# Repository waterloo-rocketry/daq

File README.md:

# Waterloo Rocketry Data Acquisition System

Work in progress repo for the next iteration of the WR DAQ. This revision focuses on modularity and extensibility, with the ability to easily add more sensors as required. Schematics of the last revision are in `old/`. The new system supports the following:
* Strain gauges
* 12V pressure transducers
* thermistors/RTDs based on need
* SD card logging using an Arduino
* Logging to an NI DAQ instrumentation module

The system is broken up into boards based on sensor type, with each board managing its own power requirements without the need for a central power board. Sensors can be added by populating more boards (and designing new ones to be added on if necessary). `docs/` will be populated as the project progresses.

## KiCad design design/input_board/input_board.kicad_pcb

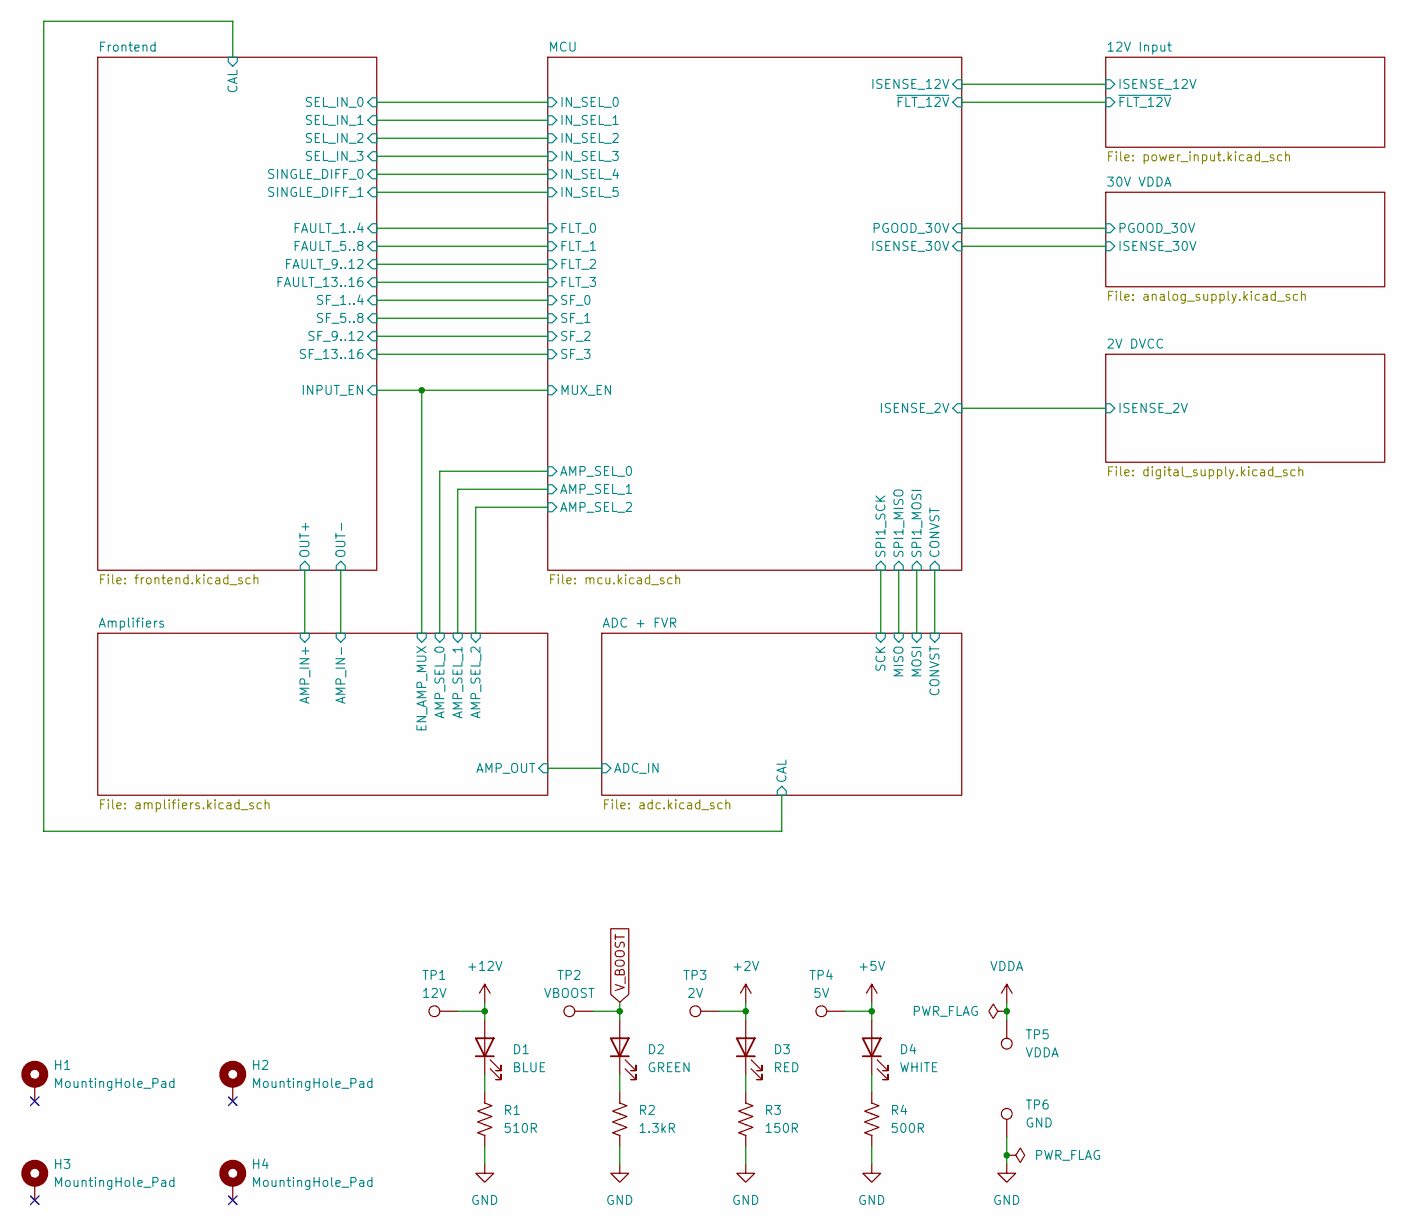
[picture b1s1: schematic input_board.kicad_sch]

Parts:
D1: BLUE; LED_1206_3216Metric_Pad1.42x1.75mm_HandSolder
D2: GREEN; LED_1206_3216Metric_Pad1.42x1.75mm_HandSolder
D3: RED; LED_1206_3216Metric_Pad1.42x1.75mm_HandSolder
D4: WHITE; LED_1206_3216Metric_Pad1.42x1.75mm_HandSolder
H1, H2, H3, H4: MountingHole_Pad; MountingHole_3.2mm_M3_DIN965_Pad
R1: 510R; R_0805_2012Metric_Pad1.20x1.40mm_HandSolder
R2: 1.3kR; R_0805_2012Metric_Pad1.20x1.40mm_HandSolder
R3: 150R; R_0805_2012Metric_Pad1.20x1.40mm_HandSolder
R4: 500R; R_0805_2012Metric_Pad1.20x1.40mm_HandSolder
TP1: 12V; TestPoint_Keystone_5000-5004_Miniature
TP2: VBOOST; TestPoint_Keystone_5000-5004_Miniature
TP3: 2V; TestPoint_Keystone_5000-5004_Miniature
TP4: 5V; TestPoint_Pad_1.5x1.5mm
TP5: VDDA; TestPoint_Keystone_5000-5004_Miniature
TP6: GND; TestPoint_Keystone_5000-5004_Miniature

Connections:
+2V: D3.2 (A), TP3.1; also elsewhere on the board
+5V: D4.2 (A), TP4.1; also elsewhere on the board
+12V: D1.2 (A), TP1.1; also elsewhere on the board
GND: R1.2, R2.2, R3.2, R4.2, TP6.1; also elsewhere on the board
unnamed: D1.1 (K), R1.1
unnamed: D2.1 (K), R2.1
unnamed: D3.1 (K), R3.1
unnamed: D4.1 (K), R4.1
VDDA: TP5.1; also elsewhere on the board
V_BOOST: D2.2 (A), TP2.1; also elsewhere on the board

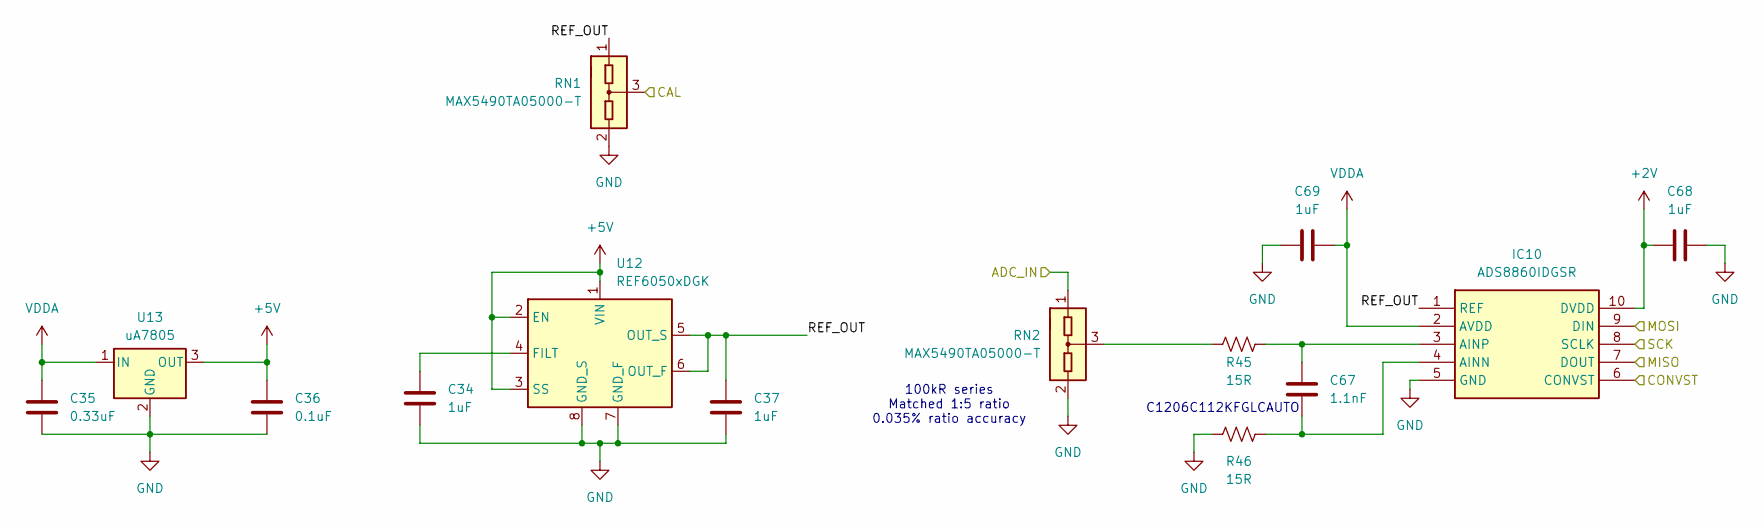
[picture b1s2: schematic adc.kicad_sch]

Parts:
C34, C37, C68, C69: 1uF; C_0805_2012Metric_Pad1.18x1.45mm_HandSolder
C35: 0.33uF; C_0805_2012Metric_Pad1.18x1.45mm_HandSolder
C36: 0.1uF; C_0805_2012Metric_Pad1.18x1.45mm_HandSolder
C67: 1.1nF; C_0805_2012Metric_Pad1.18x1.45mm_HandSolder
IC10: ADS8860IDGSR; SOP50P490X110-10N; Manufacturer_Part_Number ADS8860IDGSR; Mouser Part Number 595-ADS8860IDGSR
R45, R46: 15R; R_0805_2012Metric_Pad1.20x1.40mm_HandSolder
RN1, RN2: MAX5490TA05000-T; SOT-23
U12: REF6050xDGK; VSSOP-8_3x3mm_P0.65mm
U13: uA7805; TO-263-3_TabPin2

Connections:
+2V: C68.2, IC10.10 (DVDD); also elsewhere on the board
+5V: C36.1, U12.1 (VIN), U12.2 (EN), U12.3 (SS), U13.3 (OUT); also elsewhere on the board
/ADC + FVR/ADC_IN: RN2.1 (COM1); also elsewhere on the board
/ADC + FVR/CAL: RN1.3 (R2); also elsewhere on the board
/ADC + FVR/CONVST: IC10.6 (CONVST); also elsewhere on the board
/ADC + FVR/MISO: IC10.7 (DOUT); also elsewhere on the board
/ADC + FVR/MOSI: IC10.9 (DIN); also elsewhere on the board
/ADC + FVR/REF_OUT: C37.2, IC10.1 (REF), RN1.1 (COM1), U12.5 (OUT_S), U12.6 (OUT_F)
/ADC + FVR/SCK: IC10.8 (SCLK); also elsewhere on the board
GND: C34.1, C35.2, C36.2, C37.1, C68.1, C69.1, IC10.5 (GND), R46.2, RN1.2 (R1), RN2.2 (R1), U12.7 (GND_F), U12.8 (GND_S), U13.2 (GND); also elsewhere on the board
unnamed: C67.1, IC10.4 (AINN), R46.1
unnamed: C67.2, IC10.3 (AINP), R45.2
unnamed: R45.1, RN2.3 (R2)
unnamed: C34.2, U12.4 (FILT)
VDDA: C35.1, C69.2, IC10.2 (AVDD), U13.1 (IN); also elsewhere on the board

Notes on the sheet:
C1206C112KFGLCAUTO
100kR series Matched 1:5 ratio 0.035% ratio accuracy

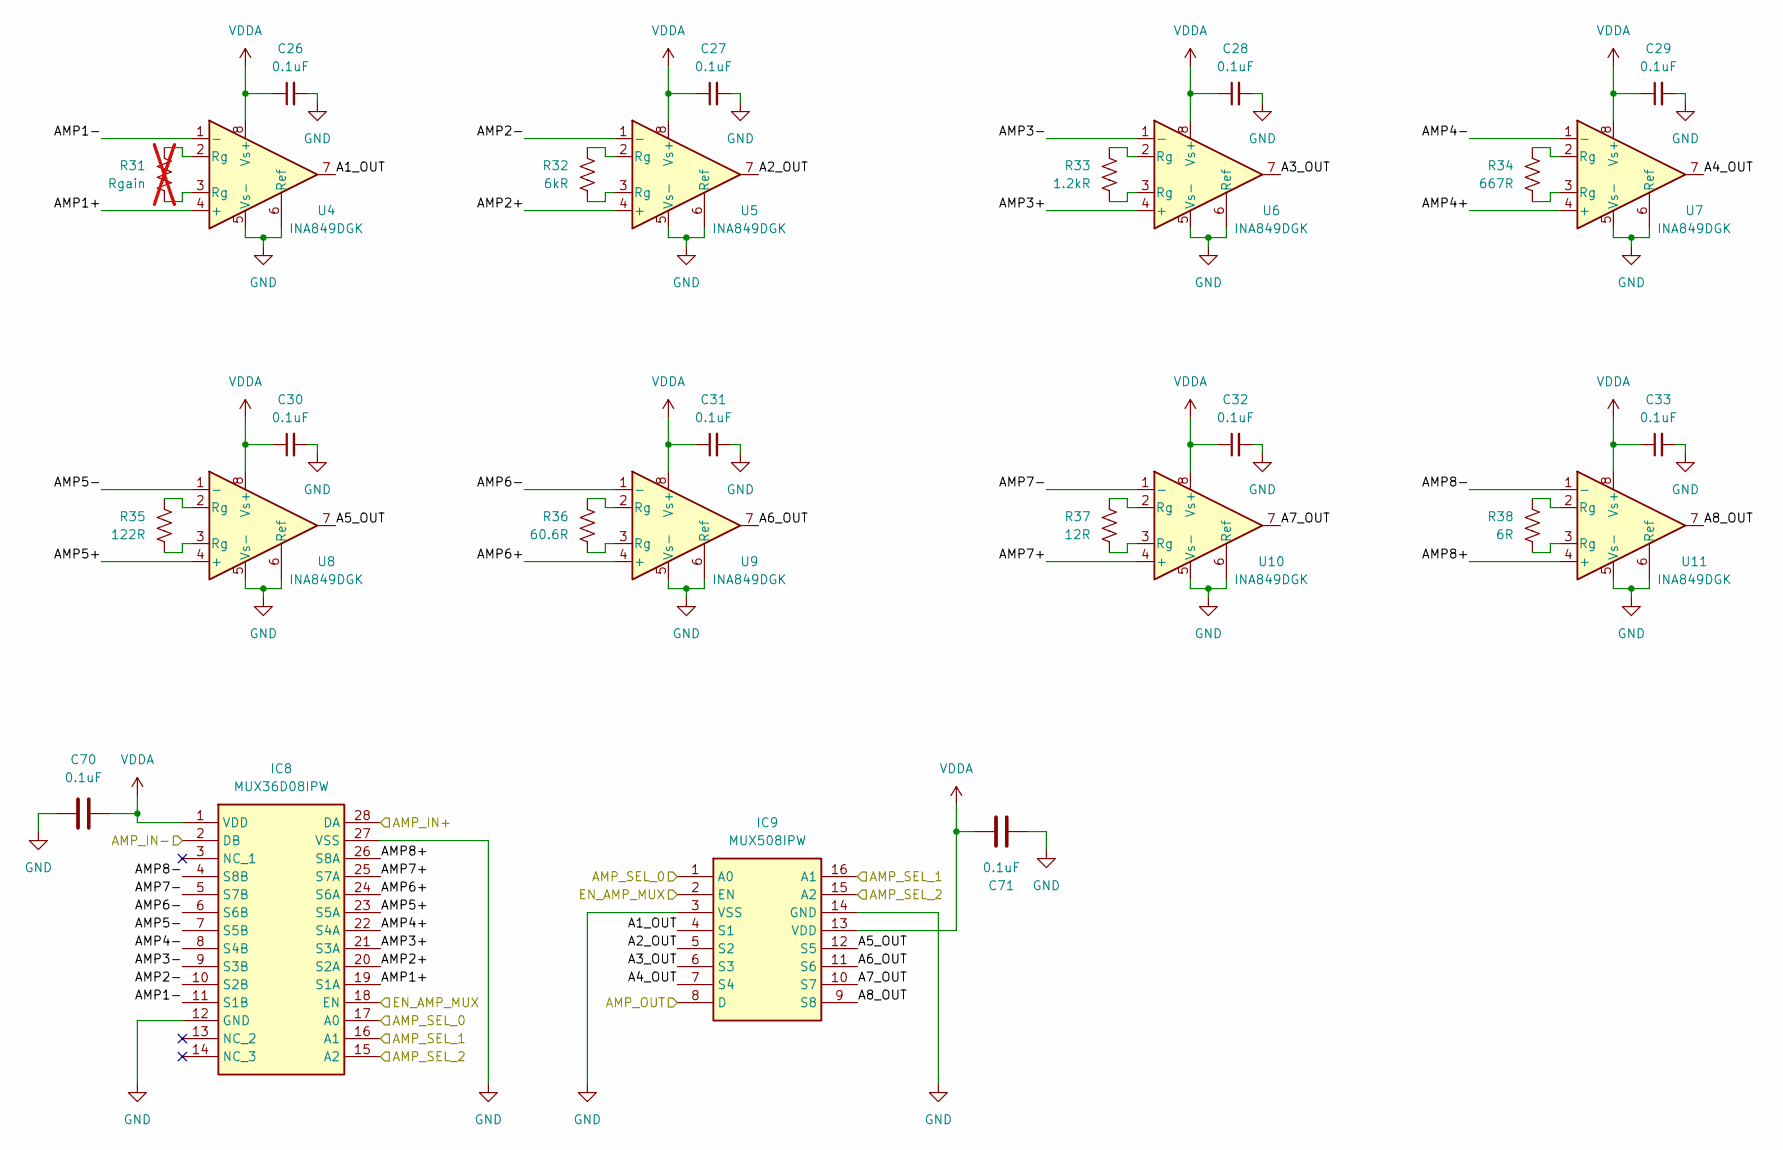
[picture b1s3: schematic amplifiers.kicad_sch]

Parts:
C26, C27, C28, C29, C30, C31, C32, C33, C70, C71: 0.1uF; C_0805_2012Metric_Pad1.18x1.45mm_HandSolder
IC8: MUX36D08IPW; SOP65P640X120-28N; Manufacturer_Part_Number MUX36D08IPW; Mouser Part Number 595-MUX36D08IPW
IC9: MUX508IPW; SOP65P640X120-16N; Manufacturer_Part_Number MUX508IPW; Mouser Part Number 595-MUX508IPW
R31: Rgain; not fitted
R32: 6kR; R_0805_2012Metric_Pad1.20x1.40mm_HandSolder
R33: 1.2kR; R_0805_2012Metric_Pad1.20x1.40mm_HandSolder
R34: 667R; R_0805_2012Metric_Pad1.20x1.40mm_HandSolder
R35: 122R; R_0805_2012Metric_Pad1.20x1.40mm_HandSolder
R36: 60.6R; R_0805_2012Metric_Pad1.20x1.40mm_HandSolder
R37: 12R; R_0805_2012Metric_Pad1.20x1.40mm_HandSolder
R38: 6R; R_0805_2012Metric_Pad1.20x1.40mm_HandSolder
U4, U5, U6, U7, U8, U9, U10, U11: INA849DGK; VSSOP-8_3x3mm_P0.65mm

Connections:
/ADC + FVR/ADC_IN: IC9.8 (D); also elsewhere on the board
/Amplifiers/A1_OUT: IC9.4 (S1), U4.7
/Amplifiers/A2_OUT: IC9.5 (S2), U5.7
/Amplifiers/A3_OUT: IC9.6 (S3), U6.7
/Amplifiers/A4_OUT: IC9.7 (S4), U7.7
/Amplifiers/A5_OUT: IC9.12 (S5), U8.7
/Amplifiers/A6_OUT: IC9.11 (S6), U9.7
/Amplifiers/A7_OUT: IC9.10 (S7), U10.7
/Amplifiers/A8_OUT: IC9.9 (S8), U11.7
/Amplifiers/AMP1+: IC8.19 (S1A), U4.4 (+)
/Amplifiers/AMP1-: IC8.11 (S1B), U4.1 (-)
/Amplifiers/AMP2+: IC8.20 (S2A), U5.4 (+)
/Amplifiers/AMP2-: IC8.10 (S2B), U5.1 (-)
/Amplifiers/AMP3+: IC8.21 (S3A), U6.4 (+)
/Amplifiers/AMP3-: IC8.9 (S3B), U6.1 (-)
/Amplifiers/AMP4+: IC8.22 (S4A), U7.4 (+)
/Amplifiers/AMP4-: IC8.8 (S4B), U7.1 (-)
/Amplifiers/AMP5+: IC8.23 (S5A), U8.4 (+)
/Amplifiers/AMP5-: IC8.7 (S5B), U8.1 (-)
/Amplifiers/AMP6+: IC8.24 (S6A), U9.4 (+)
/Amplifiers/AMP6-: IC8.6 (S6B), U9.1 (-)
/Amplifiers/AMP7+: IC8.25 (S7A), U10.4 (+)
/Amplifiers/AMP7-: IC8.5 (S7B), U10.1 (-)
/Amplifiers/AMP8+: IC8.26 (S8A), U11.4 (+)
/Amplifiers/AMP8-: IC8.4 (S8B), U11.1 (-)
/Amplifiers/AMP_IN+: IC8.28 (DA); also elsewhere on the board
/Amplifiers/AMP_IN-: IC8.2 (DB); also elsewhere on the board
/Amplifiers/AMP_SEL_0: IC8.17 (A0), IC9.1 (A0); also elsewhere on the board
/Amplifiers/AMP_SEL_1: IC8.16 (A1), IC9.16 (A1); also elsewhere on the board
/Amplifiers/AMP_SEL_2: IC8.15 (A2), IC9.15 (A2); also elsewhere on the board
/Frontend/EN_1..4: IC8.18 (EN), IC9.2 (EN); also elsewhere on the board
GND: C26.2, C27.2, C28.2, C29.2, C30.2, C31.2, C32.2, C33.2, C70.1, C71.1, IC8.12 (GND), IC8.27 (VSS), IC9.3 (VSS), IC9.14 (GND), U4.5 (Vs-), U4.6 (Ref), U5.5 (Vs-), U5.6 (Ref), U6.5 (Vs-), U6.6 (Ref), U7.5 (Vs-), U7.6 (Ref), U8.5 (Vs-), U8.6 (Ref), U9.5 (Vs-), U9.6 (Ref), U10.5 (Vs-), U10.6 (Ref), U11.5 (Vs-), U11.6 (Ref); also elsewhere on the board
unnamed: R32.1, U5.2 (Rg)
unnamed: R32.2, U5.3 (Rg)
unnamed: R33.1, U6.2 (Rg)
unnamed: R33.2, U6.3 (Rg)
unnamed: R34.1, U7.2 (Rg)
unnamed: R34.2, U7.3 (Rg)
unnamed: R35.1, U8.2 (Rg)
unnamed: R35.2, U8.3 (Rg)
unnamed: R36.1, U9.2 (Rg)
unnamed: R36.2, U9.3 (Rg)
unnamed: R37.1, U10.2 (Rg)
unnamed: R37.2, U10.3 (Rg)
unnamed: R38.1, U11.2 (Rg)
unnamed: R38.2, U11.3 (Rg)
unnamed: R31.1, U4.2 (Rg)
unnamed: R31.2, U4.3 (Rg)
VDDA: C26.1, C27.1, C28.1, C29.1, C30.1, C31.1, C32.1, C33.1, C70.2, C71.2, IC8.1 (VDD), IC9.13 (VDD), U4.8 (Vs+), U5.8 (Vs+), U6.8 (Vs+), U7.8 (Vs+), U8.8 (Vs+), U9.8 (Vs+), U10.8 (Vs+), U11.8 (Vs+); also elsewhere on the board

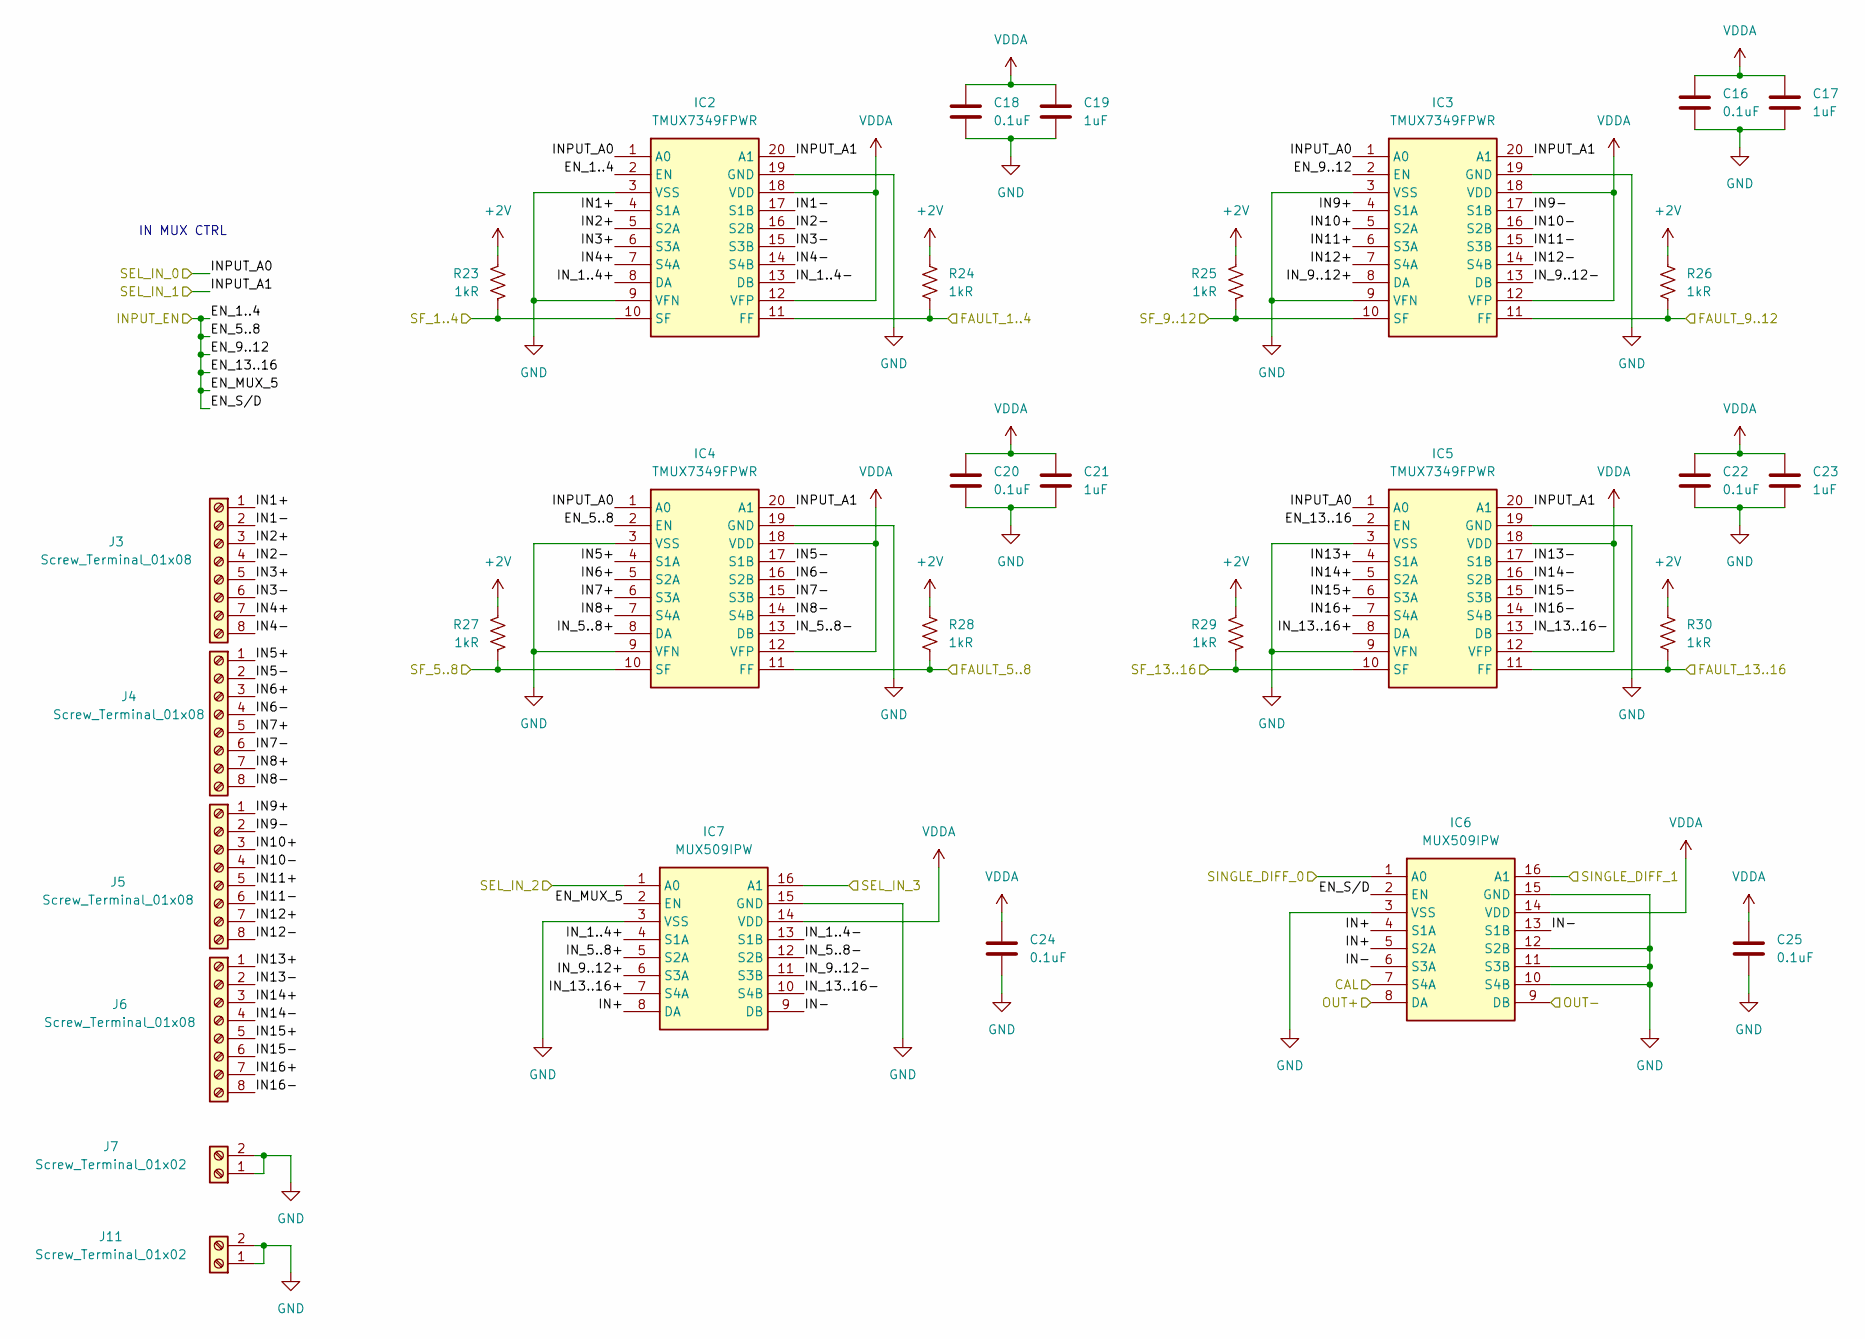
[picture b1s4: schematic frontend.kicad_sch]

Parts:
C16, C18, C20, C22, C24, C25: 0.1uF; C_0805_2012Metric_Pad1.18x1.45mm_HandSolder
C17, C19, C21, C23: 1uF; C_0805_2012Metric_Pad1.18x1.45mm_HandSolder
IC2, IC3, IC4, IC5: TMUX7349FPWR; SOP65P640X120-20N; Manufacturer_Part_Number TMUX7348FPWR; Mouser Part Number 595-TMUX7348FPWR
IC6, IC7: MUX509IPW; SOP65P640X120-16N; Manufacturer_Part_Number MUX509IPW; Mouser Part Number 595-MUX509IPW
J3, J4, J5, J6: Screw_Terminal_01x08; TerminalBlock_Phoenix_MPT-0,5-8-2.54_1x08_P2.54mm_Horizontal
J7, J11: Screw_Terminal_01x02; TerminalBlock_Phoenix_MPT-0,5-2-2.54_1x02_P2.54mm_Horizontal
R23, R24, R25, R26, R27, R28, R29, R30: 1kR; R_0805_2012Metric_Pad1.20x1.40mm_HandSolder

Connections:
+2V: R23.2, R24.2, R25.2, R26.2, R27.2, R28.2, R29.2, R30.2; also elsewhere on the board
/ADC + FVR/CAL: IC6.7 (S4A); also elsewhere on the board
/Amplifiers/AMP_IN+: IC6.8 (DA); also elsewhere on the board
/Amplifiers/AMP_IN-: IC6.9 (DB); also elsewhere on the board
/Frontend/EN_1..4: IC2.2 (EN), IC3.2 (EN), IC4.2 (EN), IC5.2 (EN), IC6.2 (EN), IC7.2 (EN); also elsewhere on the board
/Frontend/FAULT_1..4: IC2.11 (FF), R24.1; also elsewhere on the board
/Frontend/FAULT_5..8: IC4.11 (FF), R28.1; also elsewhere on the board
/Frontend/FAULT_9..12: IC3.11 (FF), R26.1; also elsewhere on the board
/Frontend/FAULT_13..16: IC5.11 (FF), R30.1; also elsewhere on the board
/Frontend/IN1+: IC2.4 (S1A), J3.1
/Frontend/IN1-: IC2.17 (S1B), J3.2
/Frontend/IN2+: IC2.5 (S2A), J3.3
/Frontend/IN2-: IC2.16 (S2B), J3.4
/Frontend/IN3+: IC2.6 (S3A), J3.5
/Frontend/IN3-: IC2.15 (S3B), J3.6
/Frontend/IN4+: IC2.7 (S4A), J3.7
/Frontend/IN4-: IC2.14 (S4B), J3.8
/Frontend/IN5+: IC4.4 (S1A), J4.1
/Frontend/IN5-: IC4.17 (S1B), J4.2
/Frontend/IN6+: IC4.5 (S2A), J4.3
/Frontend/IN6-: IC4.16 (S2B), J4.4
/Frontend/IN7+: IC4.6 (S3A), J4.5
/Frontend/IN7-: IC4.15 (S3B), J4.6
/Frontend/IN8+: IC4.7 (S4A), J4.7
/Frontend/IN8-: IC4.14 (S4B), J4.8
/Frontend/IN9+: IC3.4 (S1A), J5.1
/Frontend/IN9-: IC3.17 (S1B), J5.2
/Frontend/IN10+: IC3.5 (S2A), J5.3
/Frontend/IN10-: IC3.16 (S2B), J5.4
/Frontend/IN11+: IC3.6 (S3A), J5.5
/Frontend/IN11-: IC3.15 (S3B), J5.6
/Frontend/IN12+: IC3.7 (S4A), J5.7
/Frontend/IN12-: IC3.14 (S4B), J5.8
/Frontend/IN13+: IC5.4 (S1A), J6.1
/Frontend/IN13-: IC5.17 (S1B), J6.2
/Frontend/IN14+: IC5.5 (S2A), J6.3
/Frontend/IN14-: IC5.16 (S2B), J6.4
/Frontend/IN15+: IC5.6 (S3A), J6.5
/Frontend/IN15-: IC5.15 (S3B), J6.6
/Frontend/IN16+: IC5.7 (S4A), J6.7
/Frontend/IN16-: IC5.14 (S4B), J6.8
/Frontend/IN+: IC6.4 (S1A), IC6.5 (S2A), IC7.8 (DA)
/Frontend/IN-: IC6.6 (S3A), IC6.13 (S1B), IC7.9 (DB)
/Frontend/INPUT_A0: IC2.1 (A0), IC3.1 (A0), IC4.1 (A0), IC5.1 (A0); also elsewhere on the board
/Frontend/INPUT_A1: IC2.20 (A1), IC3.20 (A1), IC4.20 (A1), IC5.20 (A1); also elsewhere on the board
/Frontend/IN_1..4+: IC2.8 (DA), IC7.4 (S1A)
/Frontend/IN_1..4-: IC2.13 (DB), IC7.13 (S1B)
/Frontend/IN_5..8+: IC4.8 (DA), IC7.5 (S2A)
/Frontend/IN_5..8-: IC4.13 (DB), IC7.12 (S2B)
/Frontend/IN_9..12+: IC3.8 (DA), IC7.6 (S3A)
/Frontend/IN_9..12-: IC3.13 (DB), IC7.11 (S3B)
/Frontend/IN_13..16+: IC5.8 (DA), IC7.7 (S4A)
/Frontend/IN_13..16-: IC5.13 (DB), IC7.10 (S4B)
/Frontend/SEL_IN_2: IC7.1 (A0); also elsewhere on the board
/Frontend/SEL_IN_3: IC7.16 (A1); also elsewhere on the board
/Frontend/SF_1..4: IC2.10 (SF), R23.1; also elsewhere on the board
/Frontend/SF_5..8: IC4.10 (SF), R27.1; also elsewhere on the board
/Frontend/SF_9..12: IC3.10 (SF), R25.1; also elsewhere on the board
/Frontend/SF_13..16: IC5.10 (SF), R29.1; also elsewhere on the board
/Frontend/SINGLE_DIFF_0: IC6.1 (A0); also elsewhere on the board
/Frontend/SINGLE_DIFF_1: IC6.16 (A1); also elsewhere on the board
GND: C16.2, C17.2, C18.2, C19.2, C20.2, C21.2, C22.2, C23.2, C24.2, C25.2, IC2.3 (VSS), IC2.9 (VFN), IC2.19 (GND), IC3.3 (VSS), IC3.9 (VFN), IC3.19 (GND), IC4.3 (VSS), IC4.9 (VFN), IC4.19 (GND), IC5.3 (VSS), IC5.9 (VFN), IC5.19 (GND), IC6.3 (VSS), IC6.10 (S4B), IC6.11 (S3B), IC6.12 (S2B), IC6.15 (GND), IC7.3 (VSS), IC7.15 (GND), J7.1, J7.2, J11.1, J11.2; also elsewhere on the board
VDDA: C16.1, C17.1, C18.1, C19.1, C20.1, C21.1, C22.1, C23.1, C24.1, C25.1, IC2.12 (VFP), IC2.18 (VDD), IC3.12 (VFP), IC3.18 (VDD), IC4.12 (VFP), IC4.18 (VDD), IC5.12 (VFP), IC5.18 (VDD), IC6.14 (VDD), IC7.14 (VDD); also elsewhere on the board

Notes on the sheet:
IN MUX CTRL

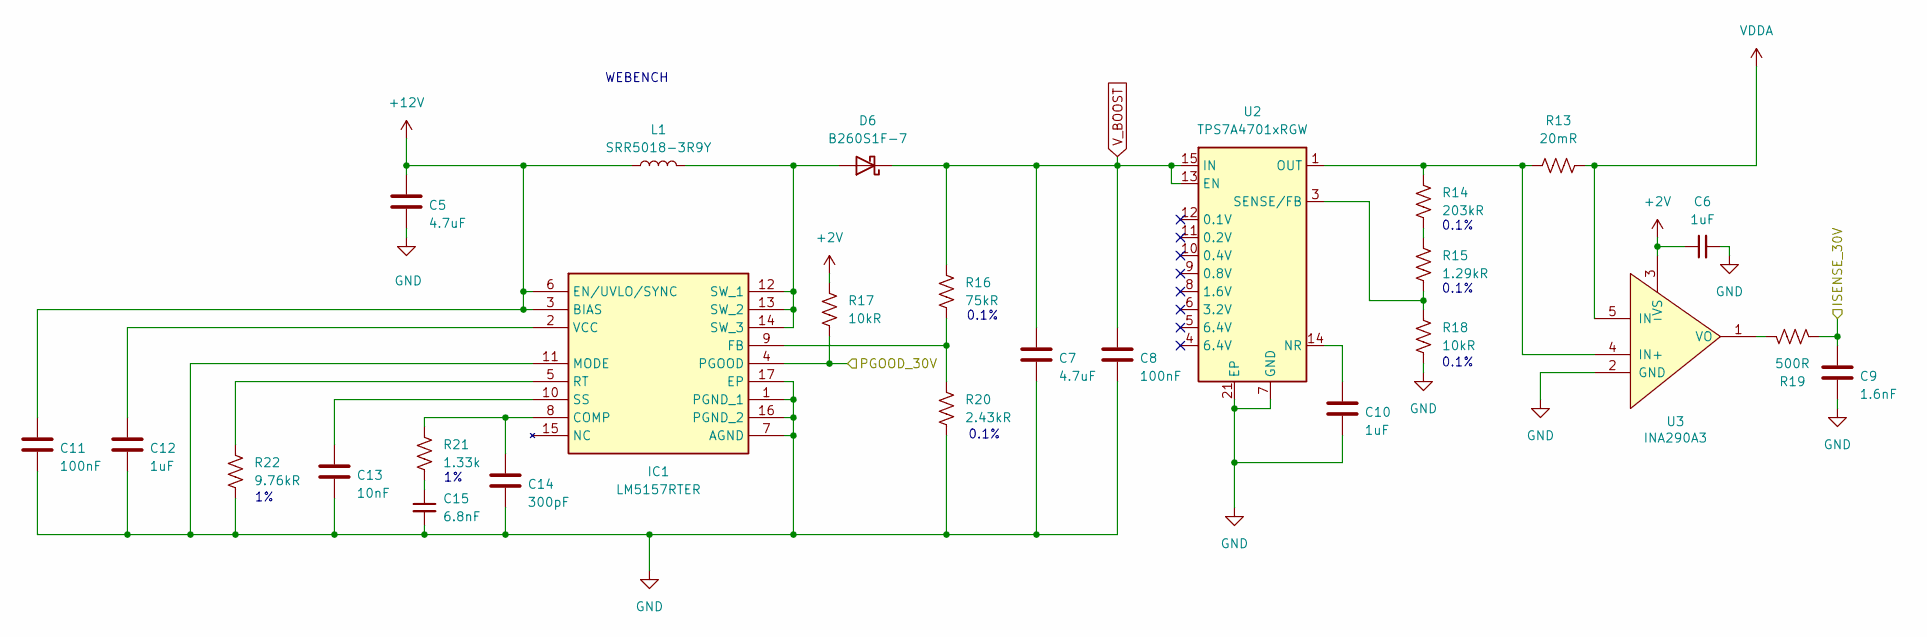
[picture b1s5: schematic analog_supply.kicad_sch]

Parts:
C5, C7: 4.7uF; C_0805_2012Metric_Pad1.18x1.45mm_HandSolder
C6, C10, C12: 1uF; C_0805_2012Metric_Pad1.18x1.45mm_HandSolder
C8, C11: 100nF; C_0805_2012Metric_Pad1.18x1.45mm_HandSolder
C9: 1.6nF; C_0805_2012Metric_Pad1.18x1.45mm_HandSolder
C13: 10nF; C_0805_2012Metric_Pad1.18x1.45mm_HandSolder
C14: 300pF; C_0805_2012Metric_Pad1.18x1.45mm_HandSolder
C15: 6.8nF; C_0805_2012Metric_Pad1.18x1.45mm_HandSolder
D6: B260S1F-7; CR_SOD123F_DIO
IC1: LM5157RTER; QFN50P300X300X80-17N-D; Manufacturer_Part_Number LM5157RTER; Mouser Part Number 595-LM5157RTER
L1: SRR5018-3R9Y; IND_BOURNS_SRR5018
R13: 20mR; R_0805_2012Metric_Pad1.20x1.40mm_HandSolder
R14: 203kR; R_0805_2012Metric_Pad1.20x1.40mm_HandSolder
R15: 1.29kR; R_0805_2012Metric_Pad1.20x1.40mm_HandSolder
R16: 75kR; R_0805_2012Metric_Pad1.20x1.40mm_HandSolder
R17, R18: 10kR; R_0805_2012Metric_Pad1.20x1.40mm_HandSolder
R19: 500R; R_0805_2012Metric_Pad1.20x1.40mm_HandSolder
R20: 2.43kR; R_0805_2012Metric_Pad1.20x1.40mm_HandSolder
R21: 1.33k; R_0805_2012Metric_Pad1.20x1.40mm_HandSolder
R22: 9.76kR; R_0805_2012Metric_Pad1.20x1.40mm_HandSolder
U2: TPS7A4701xRGW; Texas_RGW0020A_VQFN-20-1EP_5x5mm_P0.65mm_EP3.15x3.15mm_Ther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
U3: INA290A3; SC70-5_DCK_TEX

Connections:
+2V: C6.1, R17.1, U3.3 (VS); also elsewhere on the board
+12V: C5.1, C11.1, IC1.3 (BIAS), IC1.6 (EN/UVLO/SYNC), L1.1; also elsewhere on the board
/30V VDDA/ISENSE_30V: C9.1, R19.1; also elsewhere on the board
/30V VDDA/PGOOD_30V: IC1.4 (PGOOD), R17.2; also elsewhere on the board
GND: C5.2, C6.2, C7.2, C8.2, C9.2, C10.2, C11.2, C12.2, C13.2, C14.2, C15.2, IC1.1 (PGND_1), IC1.7 (AGND), IC1.11 (MODE), IC1.16 (PGND_2), IC1.17 (EP), R18.2, R20.2, R22.1, U2.7 (GND), U2.21 (EP), U3.2 (GND); also elsewhere on the board
unnamed: C15.1, R21.1
unnamed: D6.2 (A), IC1.12 (SW_1), IC1.13 (SW_2), IC1.14 (SW_3), L1.2
unnamed: C14.1, IC1.8 (COMP), R21.2
unnamed: IC1.9 (FB), R16.2, R20.1
unnamed: IC1.5 (RT), R22.2
unnamed: C13.1, IC1.10 (SS)
unnamed: C12.1, IC1.2 (VCC)
unnamed: R14.2, R15.1
unnamed: C10.1, U2.14 (NR)
unnamed: R15.2, R18.1, U2.3 (SENSE/FB)
unnamed: R13.1, R14.1, U2.1 (OUT), U2.20 (OUT), U3.4 (IN+)
unnamed: R19.2, U3.1 (VO)
VDDA: R13.2, U3.5 (IN-); also elsewhere on the board
V_BOOST: C7.1, C8.1, D6.1 (K), R16.1, U2.13 (EN), U2.15 (IN), U2.16 (IN); also elsewhere on the board

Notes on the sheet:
0.1%
WEBENCH

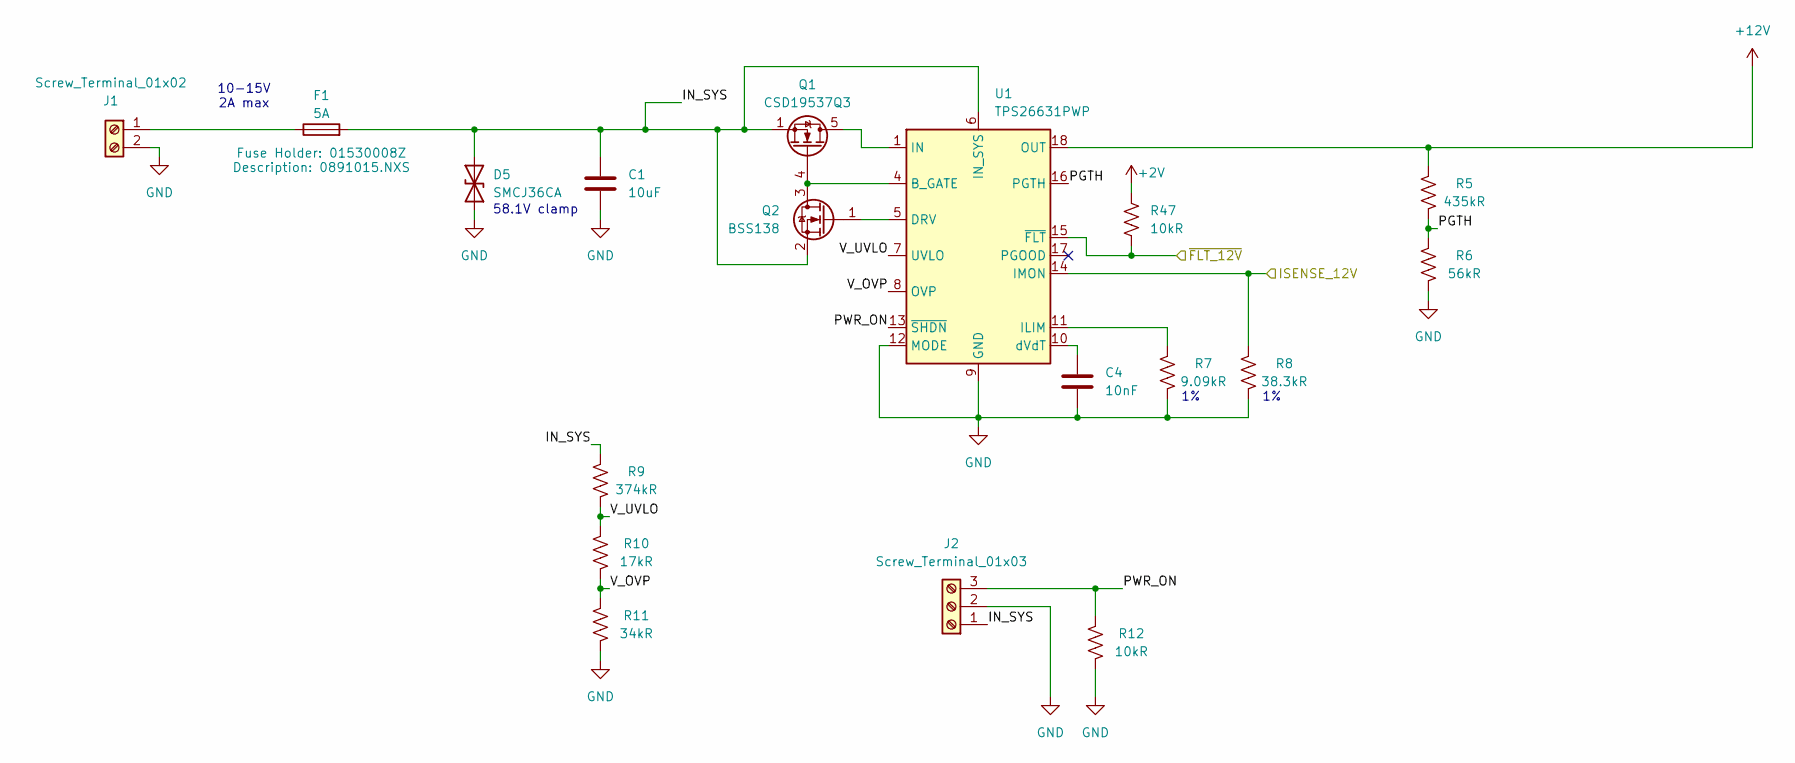
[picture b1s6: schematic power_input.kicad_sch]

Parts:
C1: 10uF; C_0805_2012Metric_Pad1.18x1.45mm_HandSolder
C4: 10nF; C_0805_2012Metric_Pad1.18x1.45mm_HandSolder
D5: SMCJ36CA; D_SMC_Handsoldering
F1: 5A; 01530009Z
J1: Screw_Terminal_01x02; TerminalBlock_Phoenix_MKDS-1,5-2-5.08_1x02_P5.08mm_Horizont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
J2: Screw_Terminal_01x03; PinHeader_1x03_P2.54mm_Vertical
Q1: CSD19537Q3; VSON-8_3.3x3.3mm_P0.65mm_NexFET
Q2: BSS138; SOT-23
R5: 435kR; R_0805_2012Metric_Pad1.20x1.40mm_HandSolder
R6: 56kR; R_0805_2012Metric_Pad1.20x1.40mm_HandSolder
R7: 9.09kR; R_0805_2012Metric_Pad1.20x1.40mm_HandSolder
R8: 38.3kR; R_0805_2012Metric_Pad1.20x1.40mm_HandSolder
R9: 374kR; R_0805_2012Metric_Pad1.20x1.40mm_HandSolder
R10: 17kR; R_0805_2012Metric_Pad1.20x1.40mm_HandSolder
R11: 34kR; R_0805_2012Metric_Pad1.20x1.40mm_HandSolder
R12, R47: 10kR; R_0805_2012Metric_Pad1.20x1.40mm_HandSolder
U1: TPS26631PWP; HTSSOP-20-1EP_4.4x6.5mm_P0.65mm_EP3.4x6.5mm_Mask2.96x2.96mm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

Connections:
+2V: R47.1; also elsewhere on the board
+12V: R5.1, U1.18 (OUT), U1.19 (OUT), U1.20 (OUT); also elsewhere on the board
/12V Input/IN_SYS: C1.1, D5.2 (A2), F1.2, J2.1, Q1.1 (S), Q1.2 (S), Q1.3 (S), Q2.2 (S), R9.1, U1.6 (IN_SYS)
/12V Input/ISENSE_12V: R8.1, U1.14 (IMON); also elsewhere on the board
/12V Input/PGTH: R5.2, R6.1, U1.16 (PGTH)
/12V Input/PWR_ON: J2.3, R12.1, U1.13 (~SHDN)
/12V Input/V_OVP: R10.2, R11.1, U1.8 (OVP)
/12V Input/V_UVLO: R9.2, R10.1, U1.7 (UVLO)
/12V Input/~FLT_12V: R47.2, U1.15 (~FLT); also elsewhere on the board
GND: C1.2, C4.2, D5.1 (A1), J1.2, J2.2, R6.2, R7.2, R8.2, R11.2, R12.2, U1.9 (GND), U1.12 (MODE), U1.21 (GND); also elsewhere on the board
unnamed: F1.1, J1.1
unnamed: Q1.5 (D), U1.1 (IN), U1.2 (IN), U1.3 (IN)
unnamed: Q1.4 (G), Q2.3 (D), U1.4 (B_GATE)
unnamed: Q2.1 (G), U1.5 (DRV)
unnamed: R7.1, U1.11 (ILIM)
unnamed: C4.1, U1.10 (dVdT)

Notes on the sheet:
10-15V 2A max
58.1V clamp

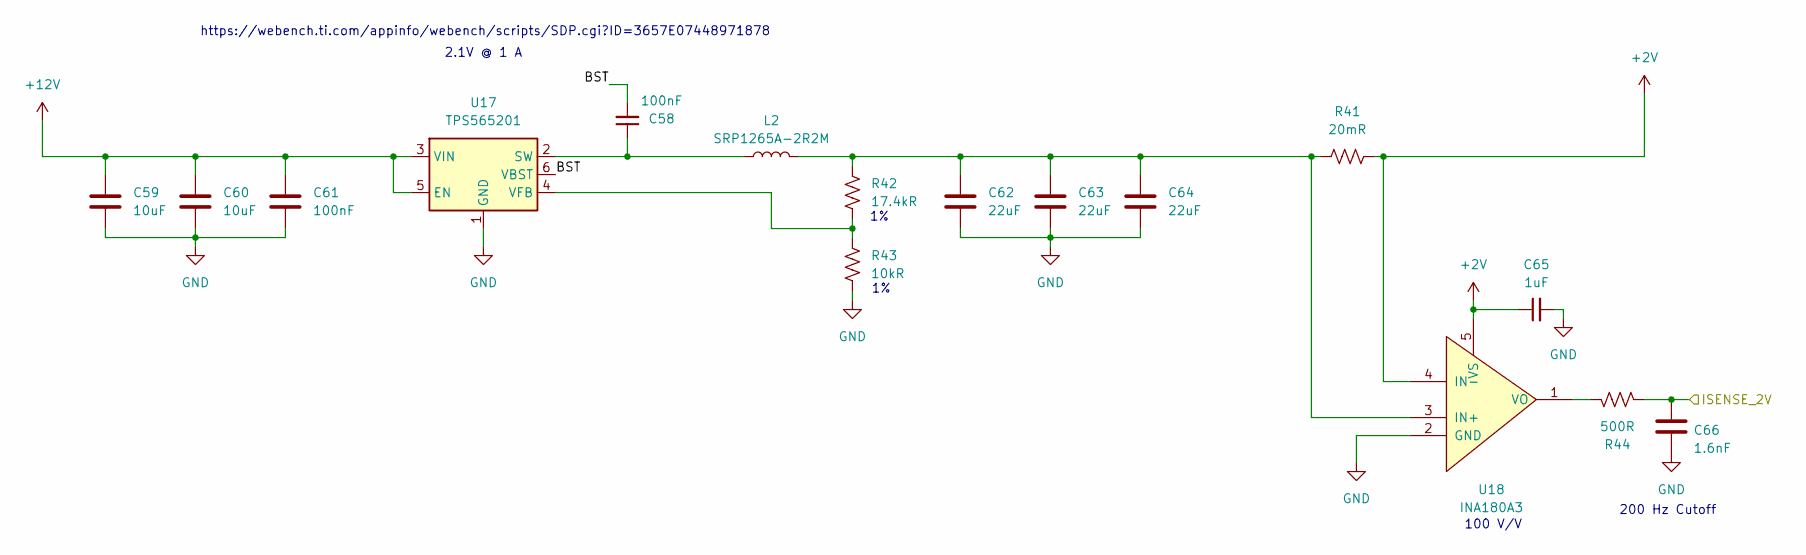
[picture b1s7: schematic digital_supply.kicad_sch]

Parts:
C58, C61: 100nF; C_0805_2012Metric_Pad1.18x1.45mm_HandSolder
C59, C60: 10uF; C_0805_2012Metric_Pad1.18x1.45mm_HandSolder
C62, C63, C64: 22uF; C_0805_2012Metric_Pad1.18x1.45mm_HandSolder
C65: 1uF; C_0805_2012Metric_Pad1.18x1.45mm_HandSolder
C66: 1.6nF; C_0805_2012Metric_Pad1.18x1.45mm_HandSolder
L2: SRP1265A-2R2M; IND_SRP1265A-2R2M
R41: 20mR; R_0805_2012Metric_Pad1.20x1.40mm_HandSolder
R42: 17.4kR; R_0805_2012Metric_Pad1.20x1.40mm_HandSolder
R43: 10kR; R_0805_2012Metric_Pad1.20x1.40mm_HandSolder
R44: 500R; R_0805_2012Metric_Pad1.20x1.40mm_HandSolder
U17: TPS565201; SOT-23-6
U18: INA180A3; SOT-23-5_HandSoldering

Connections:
+2V: C65.1, R41.2, U18.4 (IN-), U18.5 (VS); also elsewhere on the board
+12V: C59.1, C60.1, C61.1, U17.3 (VIN), U17.5 (EN); also elsewhere on the board
/2V DVCC/BST: C58.2, U17.6 (VBST)
/2V DVCC/ISENSE_2V: C66.1, R44.1; also elsewhere on the board
GND: C59.2, C60.2, C61.2, C62.2, C63.2, C64.2, C65.2, C66.2, R43.2, U17.1 (GND), U18.2 (GND); also elsewhere on the board
unnamed: C58.1, L2.1, U17.2 (SW)
unnamed: R42.2, R43.1, U17.4 (VFB)
unnamed: C62.1, C63.1, C64.1, L2.2, R41.1, R42.1, U18.3 (IN+)
unnamed: R44.2, U18.1 (VO)

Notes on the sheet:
100 V/V
https://webench.ti.com/appinfo/webench/scripts/SDP.cgi?ID=3657E07448971878
2.1V @ 1 A
200 Hz Cutoff

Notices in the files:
parts and their libraries:
Copyright 2016 Accelerated Designs. All rights reserved.
